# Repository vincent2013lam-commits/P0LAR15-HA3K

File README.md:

PR0J3CT: P0LAR1S is an OLED screen simply constructed onto a circuit board embedded in a C++ or python code that predicts the environment around you, such as temperature and humidity.

First off is the schematic design, the Raspberry Pico Microcontroller, the capacitors, connectors and resistors:

Then comes assigning the footprints, make sure you choose the right ones:

In the PCB design transferred from the Schematic, it should come out something like this:

Of course, you need to create an edge, this time adding a copper layer, and as always, wiring:

Take a look to admire the work in a 3D preview:

Then comes the sensor, adding it to the schematic, footrpints and PCB.

After comes the gerber and drill files, where you can preview the PCB on JLCPCB:

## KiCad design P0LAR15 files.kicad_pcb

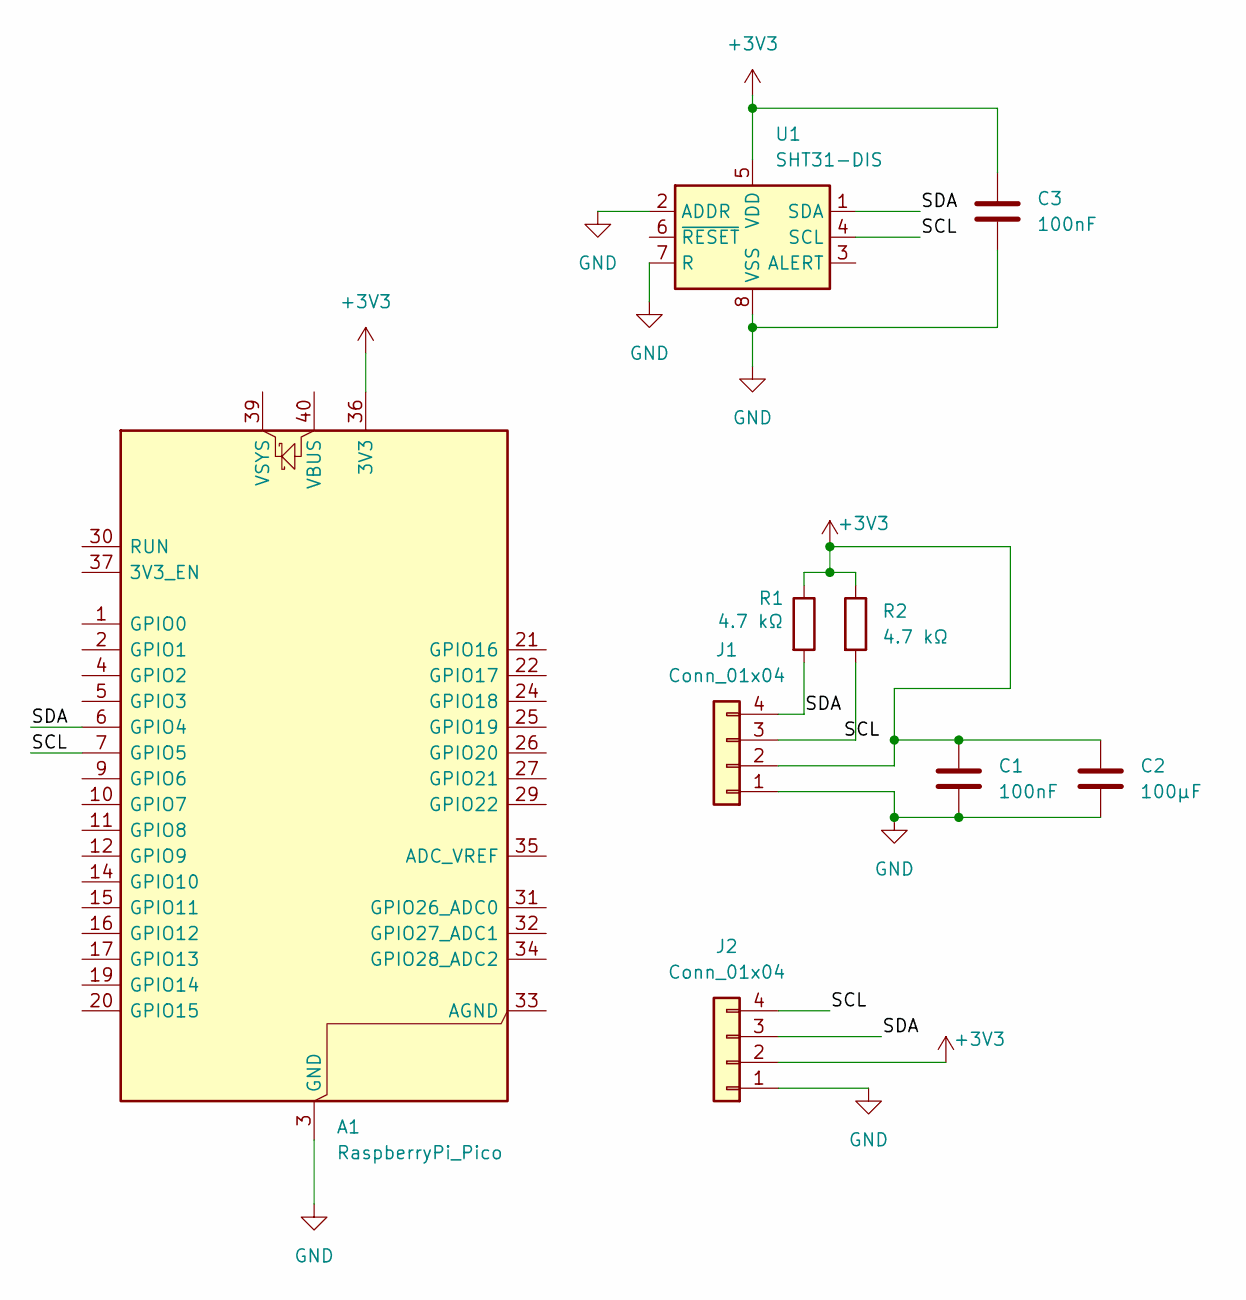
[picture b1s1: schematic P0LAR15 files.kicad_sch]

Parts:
A1: RaspberryPi_Pico; RaspberryPi_Pico_Common_Unspecified
C1, C3: 100nF; C_0805_2012Metric
C2: 100µF; C_0805_2012Metric
J1: Conn_01x04; PinSocket_1x04_P2.54mm_Vertical
J2: Conn_01x04; JST_SH_SM04B-SRSS-TB_1x04-1MP_P1.00mm_Horizontal
R1, R2: 4.7 kΩ; R_0805_2012Metric
U1: SHT31-DIS; Sensirion_DFN-8-1EP_2.5x2.5mm_P0.5mm_EP1.1x1.7mm

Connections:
+3V3: A1.36 (3V3), C1.1, C2.1, C3.1, J1.2, J2.2, R1.1, R2.1, U1.5 (VDD)
/SCL: A1.7 (GPIO5), J1.3, J2.4, R2.2, U1.4 (SCL)
/SDA: A1.6 (GPIO4), J1.4, J2.3, R1.2, U1.1 (SDA)
GND: A1.3 (GND), A1.8 (GND), A1.13 (GND), A1.18 (GND), A1.23 (GND), A1.28 (GND), A1.38 (GND), C1.2, C2.2, C3.2, J1.1, J2.1, U1.2 (ADDR), U1.7 (R), U1.8 (VSS), U1.9 (VSS)

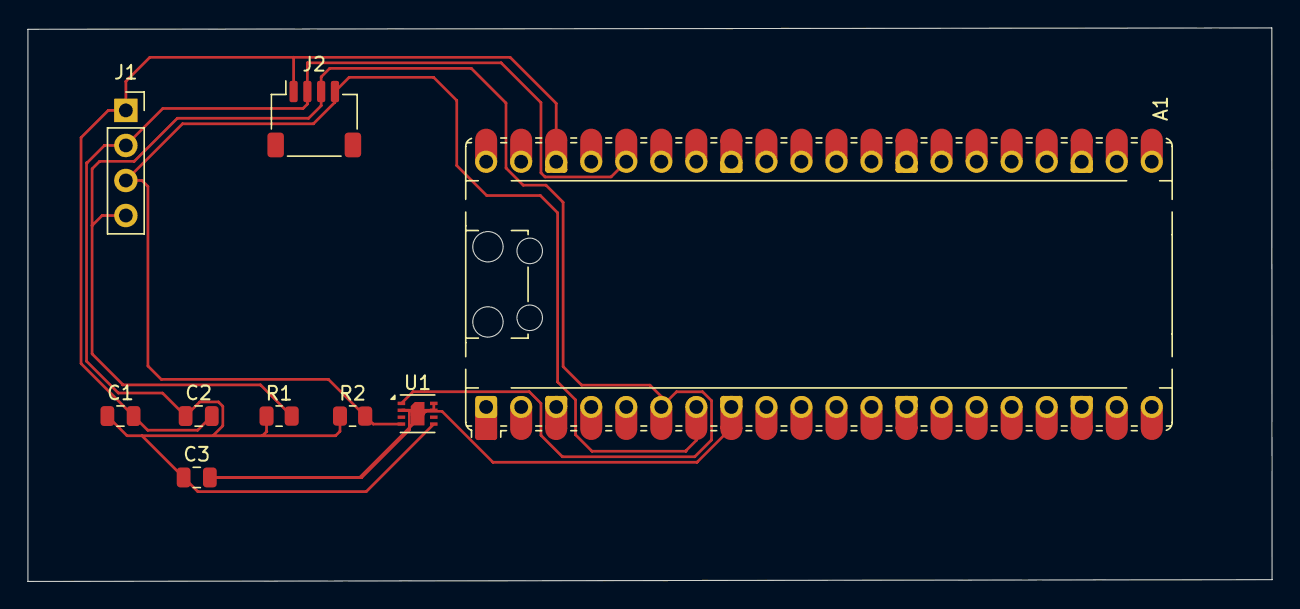
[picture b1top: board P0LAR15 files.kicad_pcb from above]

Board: 2 copper layers, 90.2 x 40.1 mm, 9 parts (0 on the bottom side), 4 nets.
